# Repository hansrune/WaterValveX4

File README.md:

# Valve Controller X4

Work in progress / still a prototype...

A DYI 4x valve controller based on ESP32c3. This device is mainly intended for irrigation control, typically using 12V solenoid valves. You can also use ball valves with automatic return on power off.

This board is tested with ESPhome and ESPEasy [firmware](#firmwares) (build instructions below), and is easily used with home automation systems that support MQTT auto discovery, the native Home Assistant API, and the many [controllers that ESPEasy supports](https://espeasy.readthedocs.io/en/latest/Controller/_Controller.html)

## Introduction

Some of the main features and benefits

- **4x outputs**
    - For controlling up to four valves at a time
    - Each valve should draw less than 1A - or you can add to the PCB trace thickness using wire
- **Flow sensor input**
    - A flow sensor input is available
    - Can be open collector / hall sensor. Pulled up to 3.3V level internally. 5V supply on terminal
- **I2C support**
    - An I2C pin header with power supply is available to use with I2C sensors
    - ... or you can use the same GPIO pins for any other purpose of your choise
- **WiFi based**
    - This is almost a must have for most home automation systems
    - OTA support
    - Configuration backup, restore and bulk updates.
- **Firmware of your choise**
    - ESPEasy with Domoticz over http. Device creation uses virtual sensors
    - ESPEasy with Domotics and Home Assistant via MQTT. Device creation uses a MQTT configuration text file.
    - ESPHome to Home Assistant via MQTT and auto discovery
    - ESPHome to Domoticz via MQTT and auto discovery
    - ... and as the hardware supports using both Arduino and ESP-IF development kits, almost any other firmware can be created.
- **Seed Studio XIAO ESP32C3**
    - This device is shielded and comes with an external IPX antenna connector
    - FCC and CE regulations approved

## Setup and mounting

The main parts includes a simple flow sensor and a pressure reduction device:

The adapter parts are [3D prints](./FreeCAD/README.md)

I use a long box with a closing / latched lid. This is designed for outdoor use. Will tolerate rain, but not frost.

Please note the bottom holes. In case water is leaked, it has a way to drain out of the box

## Indicators

Each of the four valve outputs has a LED indicator at the back of the PCB

- LED D11 will indicate low level input from the flow meter
- LED D1
  - no change indicates out of power, device death/freeze or other
  - a duty cycle 1:1 will indicate a reset is ongoing
<!--
  - will blink with a duty cycle 1-4 or 4-1 to indicate valve closed or open
-->

## Implementation and design

The schematic diagram is [available here](KiCad/WaterValveX4-schema-2.0.1.pdf). The [KiCad EDA](https://www.kicad.org/) project is in the [same folder](./KiCad)

### GPIO pin usage

| IO  | ESP32C3 | ESP32C6 | Capabilty          | Function                            |
|-----|---------|---------|--------------------|-------------------------------------|
| D0  | GPIO2   | GPIO0   | Acticve low output | LED D2 - not used                   |
| D1  | GPIO3   | GPIO1   | Active high output | Valve 1                             |
| D2  | GPIO4   | GPIO2   | Active high output | Valve 2                             |
| D3  | GPIO5   | GPIO21  | Active high output | Valve 3                             |
| D4  | GPIO6   | GPIO22  | I2C                | SDA                                 |
| D5  | GPIO7   | GPIO23  | I2C                | SCL                                 |
| D6  | GPIO21  | GPIO16  | TX / 1-wire        | Serial or 1-wire sensor             | 
| D7  | GPIO20  | GPIO17  | TX / 1-wire        | Serial or 1-wire sensor             |
| D8  | GPIO8   | GPIO19  | Active high output | Valve 4                             |
| D9  | GPIO9   | GPIO20  | Active low out     | Status LED                          |
| D10 | GPIO21  | GPIO18  | Pulled up input    | Flow meter input                    |

## Hardware - getting started

This project uses my [KiCad-lib-ESP32 repository](https://github.com/hansrune/KiCad-lib-ESP32.git) as a [git submodule](https://www.git-scm.com/book/en/v2/Git-Tools-Submodules). To check this out, use the following:

```bash
git clone --recurse-submodules https://github.com/hansrune/WaterValveX4.git 
```

### Materials used

This project uses the [Seed Studio XIAO ESP32C3 RISC-V module](https://www.seeedstudio.com/Seeed-XIAO-ESP32C3-p-5431.html). This tiny device has proven to be more reliable than most ESP8266 modules used in earlier versions. This module also comes with an IPX connector for connecting an external antenna, and is delivered with a simple external antenna for good range. This device is also EMI shielded and certified.

<!--
A ball valve like [these HSH-FLO valves](https://www.ebay.com/itm/121728665101?var=420727385309) uses metal gears, and also have a manual override possibility. Despite the moderate cost, I have found them very reliable. Manufacturer claims 100k operations. I typically use a 2 or some times 3-port version, size 3/4" DN20, DC12/24V and with CR05-01 wiring, including a manual overrride whell option.
-->
A 4x valve like the below attached with a washing machine attachment hose

A selection of 3D printable (STL and FreeCAD) adapters is available [here](./FreeCAD/README.md)

Any available 12V DC power supply delivering 2A or more should do for the control board and the valves.

There are many options and possible pinouts for DC-DC converters for the 12V to 5V conversion. A linear regulator (L7805) will need a heatsink, so a DC-DC converter is recommended.

The MOSFETs need a low Vgs trigger voltage, i.e. well under 3V on full load. I have used Si2302/N025P for the N-channel, SOT-23 package.

Resistors are 0805 size. Screw terminals are 3.5mm, which is a tight fit when ferrules are being used.

For more information, use [this KiCad BOM](KiCad/WaterValveX4-BOM.csv)

## Hardware assembly

Soldering a prototype by hand is possible if you have a steady hand and a small solder iron tip. A microscope is recommended to inspect the solder joints properly.

Recommend to do the SMD parts first, then other components. 

### Hardware tests

You should test at least the following **before adding the ESP32 module**:

- Attach a battery and check that the valve can be operated both NO and NC
- Add power and check that 5V conversion is OK
- Apply 5V to GPIO 1, 5, 3 and 8 in turn to check that the output works with the indicators at the PCB back side

## Firmwares

### ESPHome

ESPHome firmware can be set up from [this ESPHome configuration repository](https://github.com/hansrune/esphome-config) using the `test_waterx4.yaml` file as a template

Follow the [README](https://github.com/hansrune/esphome-config) for instructions on what you will likely want to change.

By default, MQTT auto discovery is being used. This should work out of the box with Home Assistant, Domoticz and other that support [Home Assistant MQTT Auto Discovery](https://www.home-assistant.io/integrations/mqtt/#mqtt-discovery)

In Home Assistant, the device has these controls. Valves are labelled a, b, c and d. The -1 is the controller instance

... and flow sensor / total counter:

### ESPEasy

ESPEasy can be used with a number of different controllers / home automation systms. A custom firmware build description is [available here](https://github.com/hansrune/ESPEasy-custom/blob/builds/custom/mega-20240822-1/README-custombuilds.md)

ESPEasy requires many settings. For configuration settings and rule files, you can upload the files from [this page](./ESPEasy/) as a starting point. Please make sure to change name, unit number, controller IP addresses, NTP, syslog host and latitude/longitude. This configuration uses both a MQTT controller and a Domoticz controller. Change to what you need.

## Bugs and tweaks

Version 2.0 of the PCB needs the flow sensor input components mounted as shown:

- A 1N4148 diode replaces R14 - cathode faces terminal connector
- A 5.1 kohm resistor replaces D7 - for a pull-up
- R12 is not mounted

<!-- 

## How to contribute

-->

## Licensing

This project is licensed under the [GNU General Public License v3.0](GNU-LICENSE-V3.txt) for the software, [CERN-OHL-W](OHL-LICENSE.txt) for the hardware, and [CC BY-SA](CC-BY-SA-LICENCE.txt) for the documentation and ideas.

<!-- 
| **Open Source Licenses** |                                                       |
| -------------------------|-------------------------------------------------------|
| Hardware                 | [CERN-OHL-W](OHL-LICENSE.txt)                         |
| Software                 | [GNU General Public License v3.0](GNU-LICENSE-V3.txt) |
| Documentation / idea     | [CC BY-SA](CC-BY-SA-LICENCE.txt)                      |
-->

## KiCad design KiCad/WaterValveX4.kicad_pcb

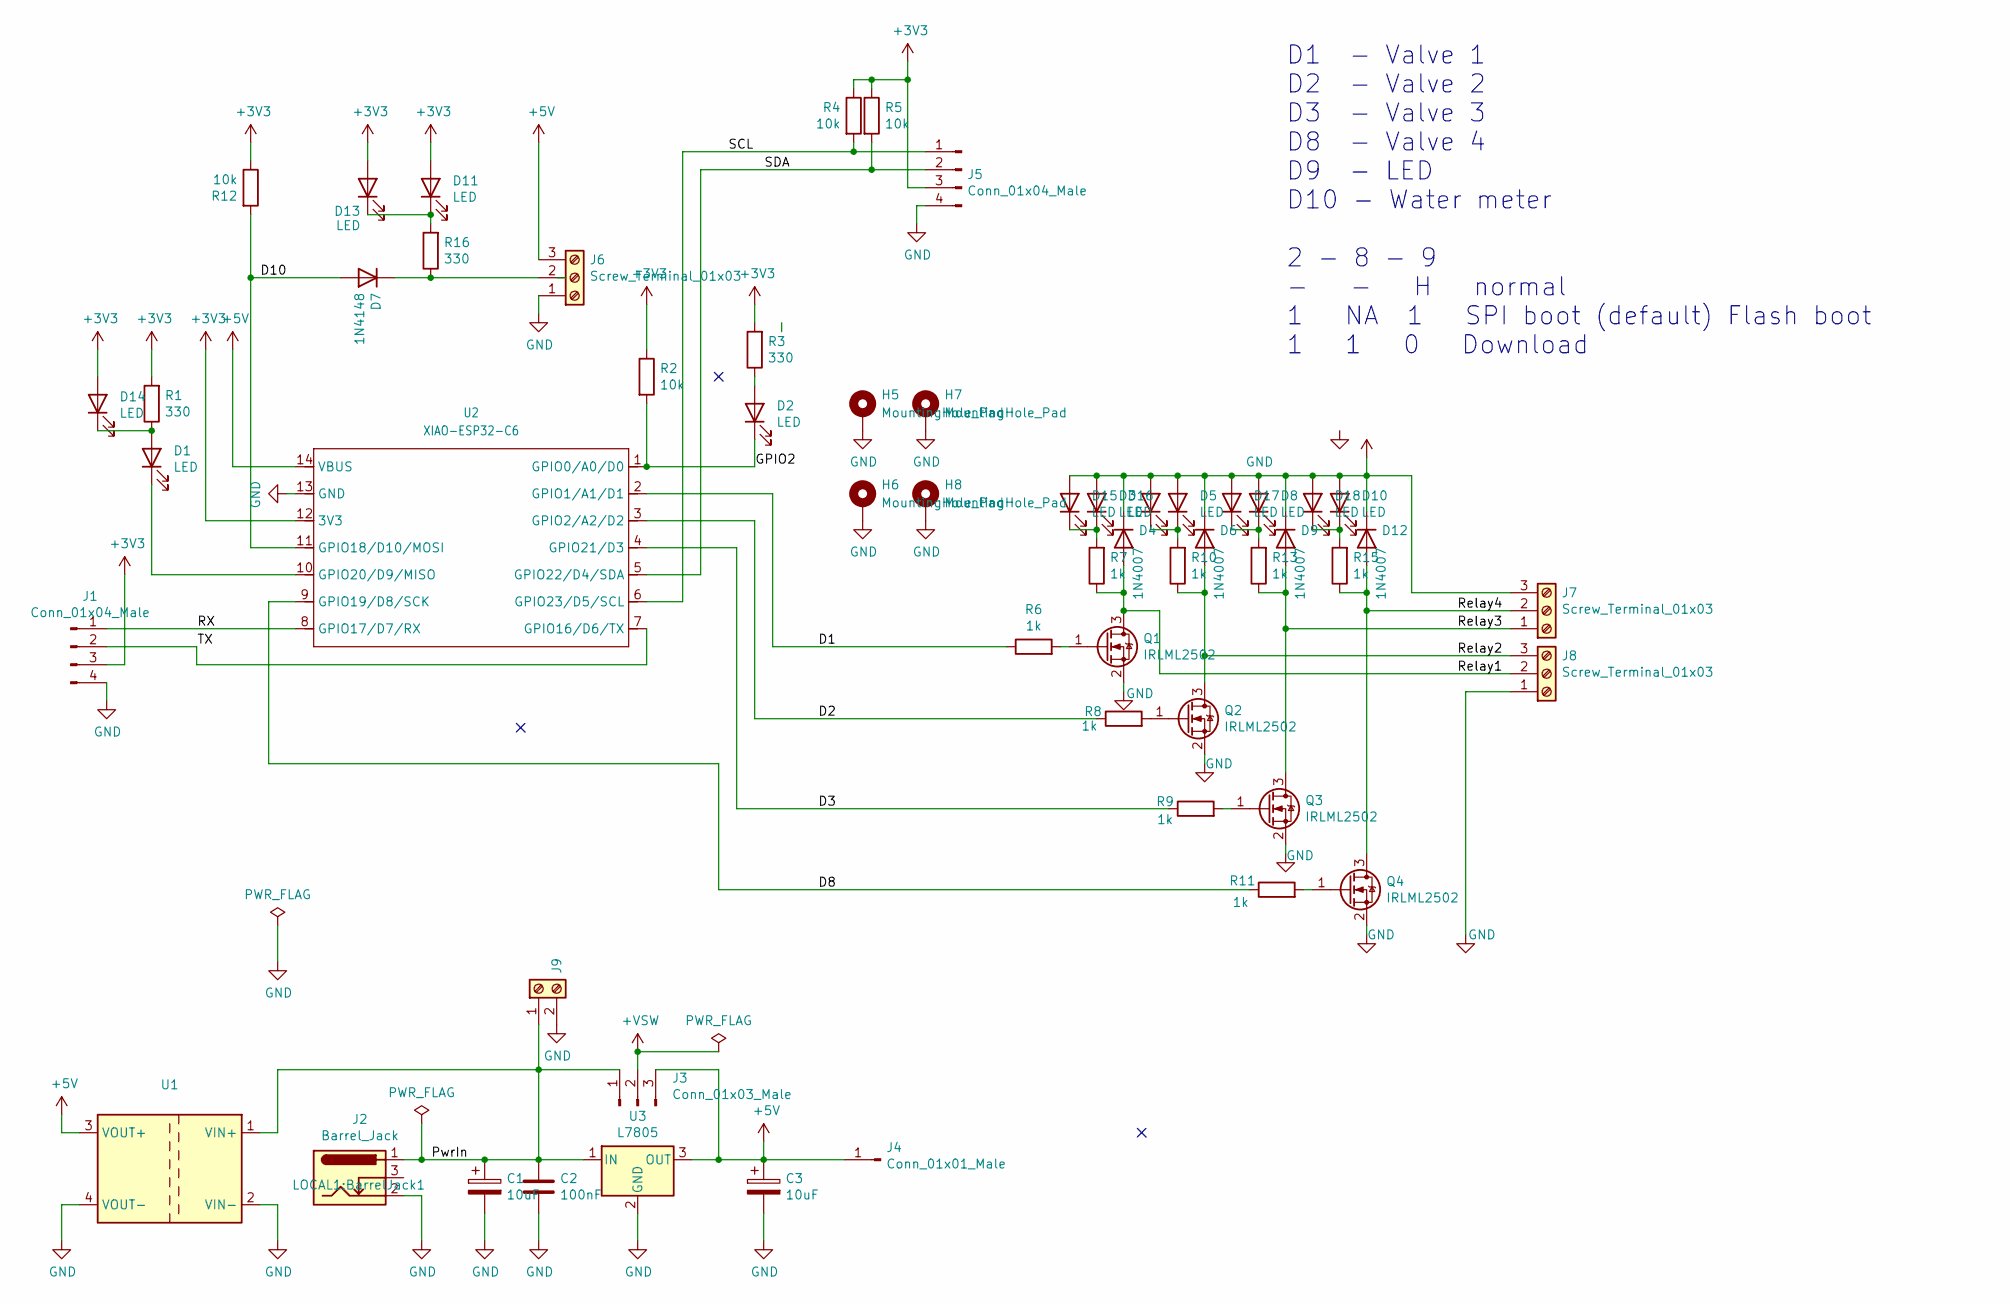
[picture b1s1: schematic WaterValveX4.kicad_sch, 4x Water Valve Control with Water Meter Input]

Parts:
C1, C3: 10uF; CP_EIA-3216-18_Kemet-A_Pad1.58x1.35mm_HandSolder
C2: 100nF; C_0805_2012Metric_Pad1.18x1.45mm_HandSolder
D1, D2, D3, D5, D8, D10, D13: LED; LED_0805_2012Metric_Pad1.15x1.40mm_HandSolder
D4, D6, D9, D12: 1N4007; D_DO-41_SOD81_P2.54mm_Vertical_KathodeUp
D7: 1N4148; D_MiniMELF
D11, D14, D15, D16, D17, D18: LED; LED_D3.0mm
H5, H6, H7, H8: MountingHole_Pad; MountingHole_3.2mm_M3_ISO14580_Pad
J1, J5: Conn_01x04_Male; PinHeader_1x04_P2.54mm_Vertical
J2: Barrel_Jack; BarrelJack1
J3: Conn_01x03_Male; PinHeader_1x03_P2.54mm_Vertical
J4: Conn_01x01_Male; PinHeader_1x01_P2.54mm_Vertical
J6, J7, J8: Screw_Terminal_01x03; TerminalBlock_Phoenix_PT-1,5-3-3.5-H_1x03_P3.50mm_Horizontal
J9: Screw_Terminal_01x02; TerminalBlock_Phoenix_PT-1,5-2-3.5-H_1x02_P3.50mm_Horizontal
Q1, Q2, Q3, Q4: IRLML2502; SOT-23_Handsoldering
R1, R3, R16: 330; R_0805_2012Metric_Pad1.20x1.40mm_HandSolder
R2, R4, R5, R12: 10k; R_0805_2012Metric_Pad1.20x1.40mm_HandSolder
R6, R7, R8, R9, R10, R11, R13, R15: 1k; R_0805_2012Metric_Pad1.20x1.40mm_HandSolder
U1: Project_DCDC_01; DCDC_01
U2: XIAO-ESP32-C6; XIAO-ESP32-C6-DIP
U3: L7805; TO-220-3_Vertical

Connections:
+3V3: D11.2 (A), D13.2 (A), D14.2 (A), J1.3, J5.3, R1.2, R2.1, R3.2, R4.1, R5.1, R12.1, U2.12 (3V3)
+5V: C3.1, J3.3, J4.1, J6.3, U1.3 (VOUT+), U2.14 (VBUS), U3.3 (OUT)
+VSW: D3.2 (A), D4.1 (K), D5.2 (A), D6.1 (K), D8.2 (A), D9.1 (K), D10.2 (A), D12.1 (K), D15.2 (A), D16.2 (A), D17.2 (A), D18.2 (A), J3.2, J7.3
/D1: R6.1, U2.2 (GPIO1/A1/D1)
/D2: R8.1, U2.3 (GPIO2/A2/D2)
/D3: R9.1, U2.4 (GPIO21/D3)
/D8: R11.1, U2.9 (GPIO19/D8/SCK)
/D10: D7.2 (A), R12.2, U2.11 (GPIO18/D10/MOSI)
/GPIO2: D2.1 (K), R2.2, U2.1 (GPIO0/A0/D0)
/PwrIn: C1.1, C2.1, J2.1, J3.1, J9.1, U1.1 (VIN+), U3.1 (IN)
/RX: J1.1, U2.8 (GPIO17/D7/RX)
/Relay1: D4.2 (A), J8.2, Q1.3 (D), R7.1
/Relay2: D6.2 (A), J8.3, Q2.3 (D), R10.1
/Relay3: D9.2 (A), J7.1, Q3.3 (D), R13.1
/Relay4: D12.2 (A), J7.2, Q4.3 (D), R15.1
/SCL: J5.1, R4.2, U2.6 (GPIO23/D5/SCL)
/SDA: J5.2, R5.2, U2.5 (GPIO22/D4/SDA)
/TX: J1.2, U2.7 (GPIO16/D6/TX)
GND: C1.2, C2.2, C3.2, H5.1, H6.1, H7.1, H8.1, J1.4, J2.2, J5.4, J6.1, J8.1, J9.2, Q1.2 (S), Q2.2 (S), Q3.2 (S), Q4.2 (S), U1.2 (VIN-), U1.4 (VOUT-), U2.13 (GND), U3.2 (GND)
unnamed: D1.2 (A), D14.1 (K), R1.1
unnamed: D1.1 (K), U2.10 (GPIO20/D9/MISO)
unnamed: D2.2 (A), R3.1
unnamed: D7.1 (K), J6.2, R16.1
unnamed: D10.1 (K), D18.1 (K), R15.2
unnamed: D11.1 (K), D13.1 (K), R16.2
unnamed: D3.1 (K), D15.1 (K), R7.2
unnamed: D5.1 (K), D16.1 (K), R10.2
unnamed: D8.1 (K), D17.1 (K), R13.2
unnamed: Q1.1 (G), R6.2
unnamed: Q2.1 (G), R8.2
unnamed: Q3.1 (G), R9.2
unnamed: Q4.1 (G), R11.2

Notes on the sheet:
D1 - Valve 1 D2 - Valve 2 D3 - Valve 3 D8 - Valve 4 D9 - LED D10 - Water meter 2 - 8 - 9 - - H normal 1 NA 1 SPI boot (default) Flash boot 1 1 0 Download

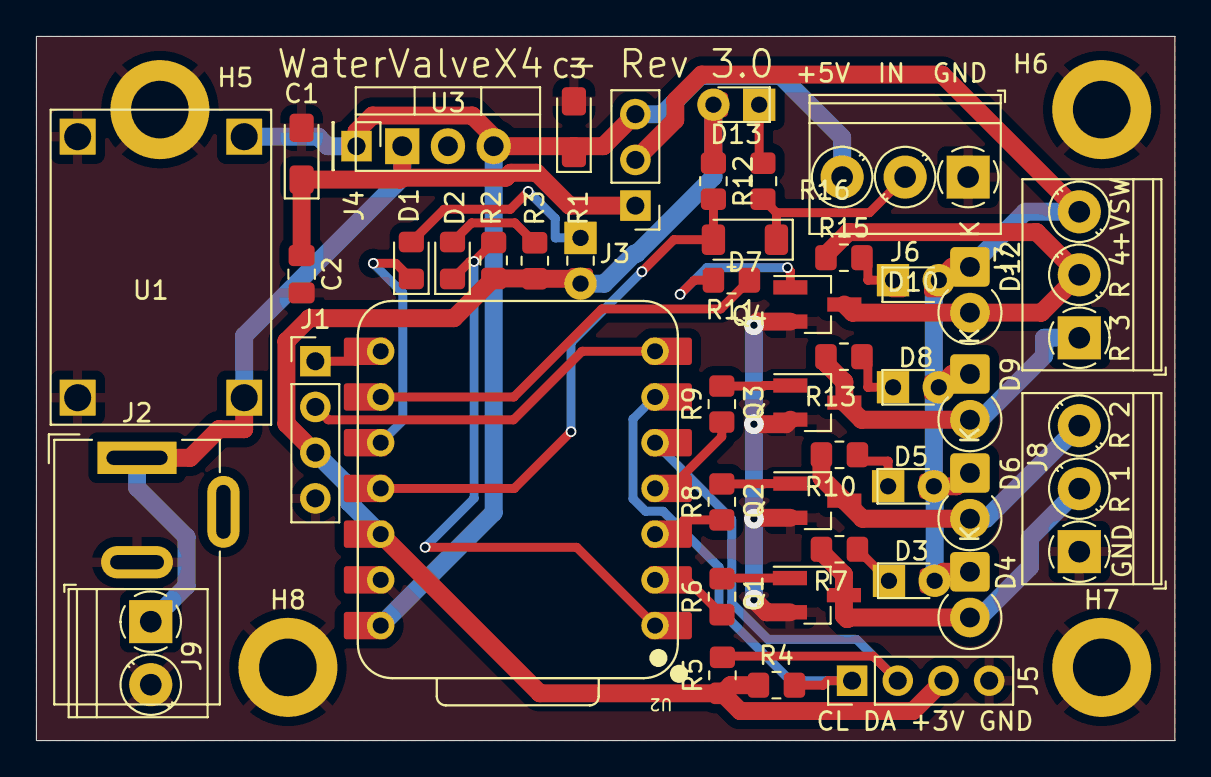
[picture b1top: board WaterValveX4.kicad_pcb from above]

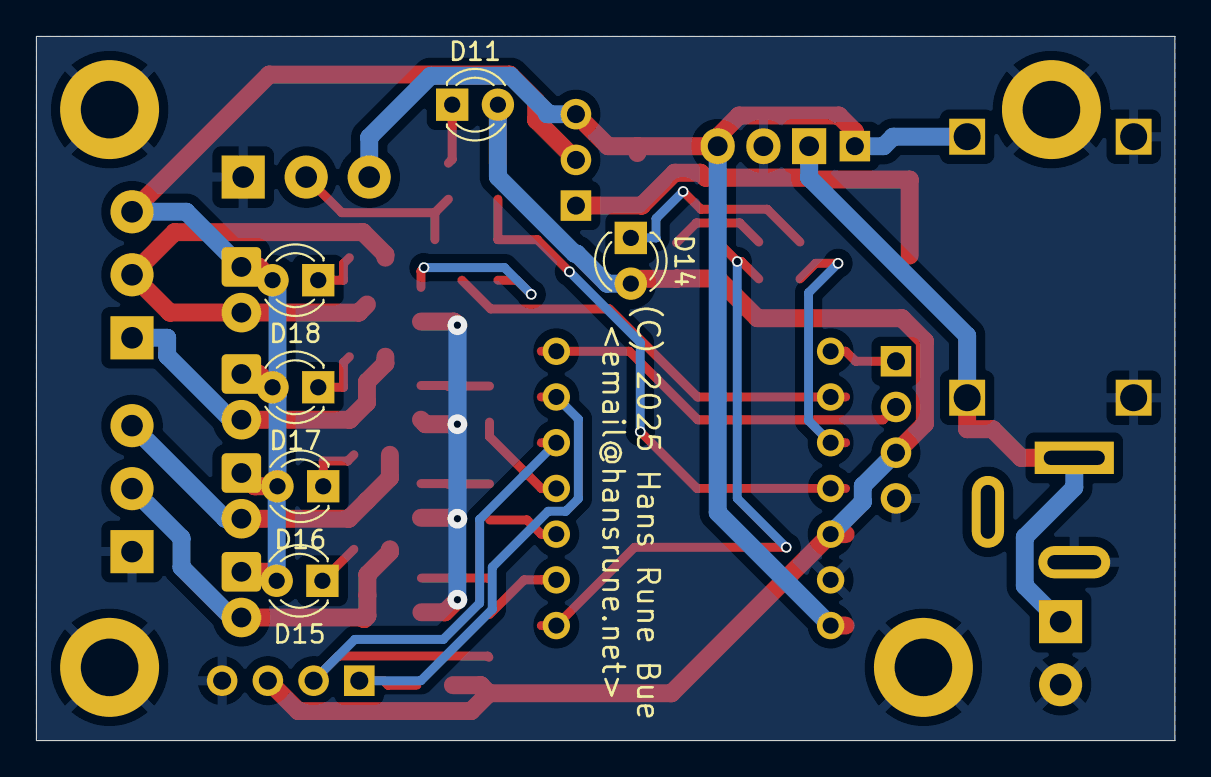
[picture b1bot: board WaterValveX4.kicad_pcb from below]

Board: 2 copper layers, 63.2 x 39.1 mm, 56 parts (6 on the bottom side), 32 nets.

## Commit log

2024-06-28 Version 2.0 - intial git version
2024-06-28 Version 2.0.1 - pulled up / level shifted flow input
2024-06-30 Add version 2.0.1 schema PDF print
2024-09-19 New 3D model
2024-10-07 Updated licensing files
2024-10-07 Added ESPEasy config
2024-10-07 Fixed KiCAD GPIO labels
2024-10-07 Added images
2024-10-07 README updates
2024-10-07 Added ESPHome support
2024-10-11 Wrong github repo reference
2025-06-14 Update README.md - no ball valve used
2025-06-27 Added 3D parts
2025-06-27 Added images and README updates
2025-06-27 Pipe adapter images added
2025-06-27 Typo...
2025-06-27 Added README for the 3D print adapters
2025-06-28 Image did not render
2025-09-30 Change to use ESP32 C6 THT
2025-10-01 Optimized layout - passes most DRC checks
2025-10-01 Update README with C3 and C6 pin names
2025-10-02 Table update in README

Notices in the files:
KiCad/WaterValveX4.kicad_pcb:
(C) 2025 Hans Rune Bue
KiCad/WaterValveX4.kicad_sch:
Copyright - Hans Rune Bue
Hardware is licensed under CERN-OHL-W-2.0
Project documents are licensed under CC-BY-SA 2.0
